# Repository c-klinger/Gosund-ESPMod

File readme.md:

# Gosund-ESPMod
The ESP12F branch is a small tweak from the original ESP-M2 adapter work to fit ESP-12F modules instead. Most of what comes after is from the original branch.

Adapter PCB to replace the CUCO-Z0 Modules on newer Gosund Smart Plugs with ESP-12F Modules. Enables to use custom firmware like [Tasmota](https://tasmota.github.io/docs/) again.

[Schematics](https://github.com/nutsoh/Gosund-ESPMod/blob/9bdc381ff534afd5aa08f2cfda641b2d8495a1db/gosund-esp-adapter.pdf)

The PCB features a Solder Jumper on the back side to control the pin mapping. 

## Tested Devices

### Gosund SP112, SP112_MAIN_AI_V1.0.

**PCB:** IO16 and JP1 have to be shorted.

**Tasmota Template:** ``{"NAME":"Gosund SP112 ESP-M2","GPIO":[288,0,289,0,2656,2720,0,0,2624,257,224,0,32,0],"FLAG":0,"BASE":18}``

## PCB Specification
- Dimension: 20.3 mm * 18.7 mm
- PCB Thickness: 0.8mm

## Bill of Material

| Pos | References | Description | Value | Size | Quantity | Order Links \* | Notes |
|-----|------------|-------------|-------|------|----------|-------------|-------|
| 01 | U1 | ESP8285:ESP-M2 |  | ESP-M2 | 1 | [Aliexpress](https://s.click.aliexpress.com/e/_DFF7SI1) | |
| 02 | C1 | Capacitor | 100nF | 0805 | 1 | [Aliexpress](https://s.click.aliexpress.com/e/_DCEFDlb) | |
| 03 | R1, R2, R3, R4 | Resistor | 10k | 0805 | 4 | [Aliexpress](https://s.click.aliexpress.com/e/_DFfLtiN)  | 

\* *I have not tested all parts using this order links, no guarantee that every linked component works. Aliexpress links are affiliate links, so i will get a small commission when you order using this link. This will help me with further projects. Thanks.*

## LICENSE

All content in this repository is is licensed under a [Creative Commons Attribution-NonCommercial-ShareAlike 4.0 International license](https://creativecommons.org/licenses/by-nc-sa/4.0/).

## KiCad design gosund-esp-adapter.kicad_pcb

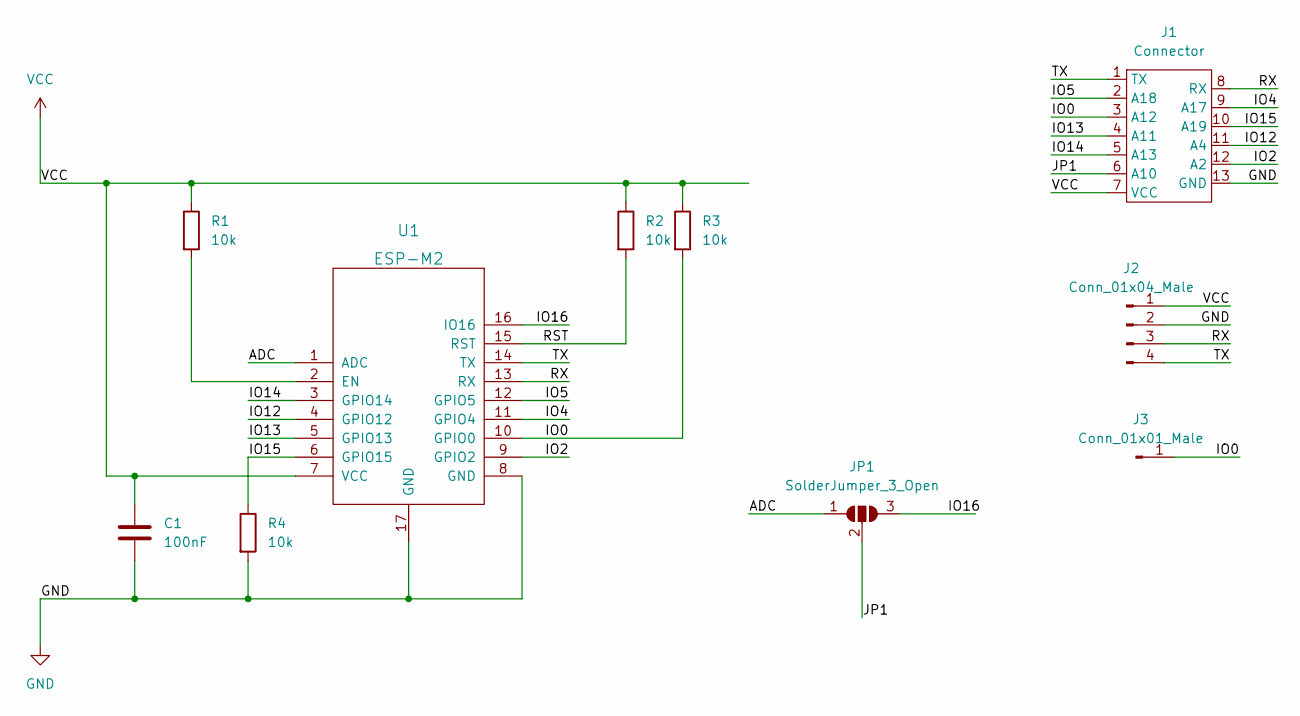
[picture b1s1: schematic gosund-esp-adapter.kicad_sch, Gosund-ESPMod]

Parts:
C1: 100nF; C_0805_2012Metric_Pad1.18x1.45mm_HandSolder
J1: Connector; PCBConnector
J2: Conn_01x04_Male; FDTI
J3: Conn_01x01_Male; IO0
JP1: SolderJumper_3_Open; SolderJumper-3_P1.3mm_Open_Pad1.0x1.5mm
R1, R2, R3, R4: 10k; R_0805_2012Metric_Pad1.20x1.40mm_HandSolder
U1: ESP-M2

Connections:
/ADC: JP1.1 (A), U1.1 (ADC); also elsewhere on the board
/IO0: J1.3 (A12), J3.1, R3.2, U1.10 (GPIO0); also elsewhere on the board
/IO2: J1.12 (A2), U1.9 (GPIO2); also elsewhere on the board
/IO4: J1.9 (A17), U1.11 (GPIO4); also elsewhere on the board
/IO5: J1.2 (A18), U1.12 (GPIO5); also elsewhere on the board
/IO12: J1.11 (A4), U1.4 (GPIO12); also elsewhere on the board
/IO13: J1.4 (A11), U1.5 (GPIO13); also elsewhere on the board
/IO14: J1.5 (A13), U1.3 (GPIO14); also elsewhere on the board
/IO15: J1.10 (A19), R4.1, U1.6 (GPIO15); also elsewhere on the board
/IO16: JP1.3 (B), U1.16 (IO16); also elsewhere on the board
/JP1: J1.6 (A10), JP1.2 (C)
/RX: J1.8 (RX), J2.3, U1.13 (RX); also elsewhere on the board
/TX: J1.1 (TX), J2.4, U1.14 (TX); also elsewhere on the board
GND: C1.2, J1.13 (GND), J2.2, R4.2, U1.8 (GND), U1.17 (GND); also elsewhere on the board
unnamed 14: R1.2, U1.2 (EN); also elsewhere on the board
unnamed 15: R2.2, U1.15 (RST); also elsewhere on the board
VCC: C1.1, J1.7 (VCC), J2.1, R1.1, R2.1, R3.1, U1.7 (VCC); also elsewhere on the board

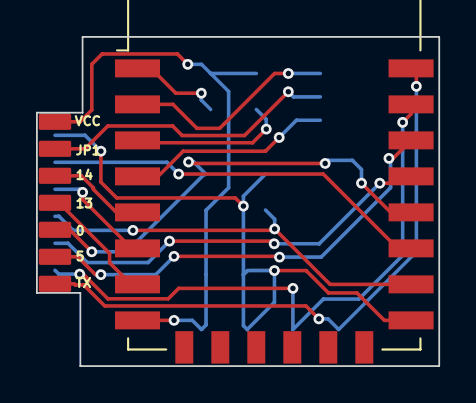
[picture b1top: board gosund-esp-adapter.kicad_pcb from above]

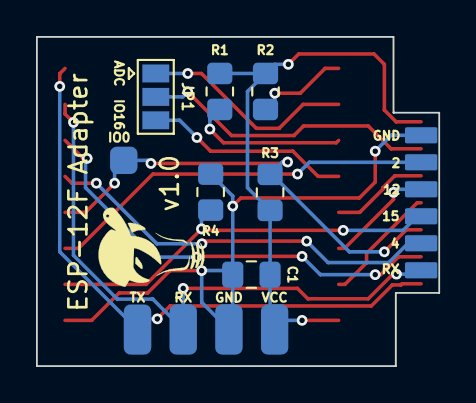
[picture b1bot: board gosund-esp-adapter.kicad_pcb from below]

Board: 2 copper layers, 22.4 x 18.3 mm, 10 parts (8 on the bottom side), 17 nets.

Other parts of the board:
U2: ESP-12F; ESP-12E

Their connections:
/ADC: U2.2 (ADC); also elsewhere on the board
/IO0: U2.18 (GPIO0); also elsewhere on the board
/IO2: U2.17 (GPIO2); also elsewhere on the board
/IO4: U2.19 (GPIO4); also elsewhere on the board
/IO5: U2.20 (GPIO5); also elsewhere on the board
/IO12: U2.6 (GPIO12); also elsewhere on the board
/IO13: U2.7 (GPIO13); also elsewhere on the board
/IO14: U2.5 (GPIO14); also elsewhere on the board
/IO15: U2.16 (GPIO15); also elsewhere on the board
/IO16: U2.4 (GPIO16); also elsewhere on the board
/RX: U2.21 (GPIO3/RXD); also elsewhere on the board
/TX: U2.22 (GPIO1/TXD); also elsewhere on the board
GND: U2.15 (GND); also elsewhere on the board
unnamed 14: U2.3 (EN); also elsewhere on the board
unnamed 15: U2.1 (~RST); also elsewhere on the board
VCC: U2.8 (VCC); also elsewhere on the board

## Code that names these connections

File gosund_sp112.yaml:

# Gosund SP112 smart plug with power sensor

# Enable Web server
web_server:
  port: 80
#
substitutions:
  plug_name: wifiplug
  # Higher value gives lower watt readout
  current_res: "0.0012"
  # Lower value gives lower voltage readout
  voltage_div: "771"
#
esphome:
  name: ${plug_name}
  platform: ESP8266
  board: esp12e

# WiFi connection
wifi:
  networks:
  - ssid: "<redacted>"
    password: "<redacted>"

  # Optional manual IP
#  manual_ip:
#    static_ip: 172.20.10.8
#    gateway: 172.20.10.1
#    subnet: 255.255.255.0

  # Enable fallback hotspot (captive portal) in case wifi connection fails
  ap:
    ssid: "${plug_name}_AP"
    password: "${plug_name}"

captive_portal:


# Enable logging
logger:

# Enable Home Assistant API
api:

ota:

time:
  - platform: homeassistant
    id: homeassistant_time

binary_sensor:
  - platform: gpio
    pin:
      number: GPIO16
      inverted: false
    name: "${plug_name}_Button"
    on_press:
      - switch.toggle: mains_relay

switch:
- platform: gpio
  name: "${plug_name}_Mains_Relay"
  id: mains_relay
  pin: GPIO14
  restore_mode: ALWAYS_ON
- platform: gpio
  name: "${plug_name}_USB_Relay"
  pin: GPIO13
  inverted: true
  restore_mode: ALWAYS_ON
- platform: gpio
  name: "${plug_name}_LED_Blue"
  pin: GPIO15
  inverted: True
  restore_mode: ALWAYS_OFF
- platform: gpio
  name: "${plug_name}_LED_Red"
  pin: GPIO00
  inverted: True
  restore_mode: ALWAYS_OFF
sensor:
  - platform: hlw8012
    sel_pin:
      number: GPIO12
      inverted: True
    cf_pin: GPIO05
    cf1_pin: GPIO04
    current_resistor: ${current_res}
    voltage_divider: ${voltage_div}
    change_mode_every: 3
    update_interval: 5s
    current:
      name: "${plug_name}_Amperage"
      unit_of_measurement: A
      accuracy_decimals: 3
    voltage:
      name: "${plug_name}_Voltage"
      unit_of_measurement: V
      accuracy_decimals: 1
    power:
      name: "${plug_name}_Wattage"
      unit_of_measurement: W
      accuracy_decimals: 0
      filters:
      - multiply: 0.5
      id: "${plug_name}_Wattage"
  - platform: total_daily_energy
    name: "${plug_name}_Total Daily Energy"
    power_id: "${plug_name}_Wattage"
    filters:
        # Multiplication factor from W to kW is 0.001
        - multiply: 0.001
    unit_of_measurement: kWh

# Extra sensor to keep track of plug uptime
  - platform: uptime
    name: ${plug_name}_Uptime Sensor

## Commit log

2023-05-02 fixed readme
2024-02-28 modified to match the footprint of an ESP12f module
2024-03-02 updating some images and docs to match the ESP12F version
2024-03-02 adding ESPHome configuration file
2024-03-03 updating gerber files to the esp12f version
